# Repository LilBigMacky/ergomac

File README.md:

# ergomac
custom split ergonomic keyboard pcb

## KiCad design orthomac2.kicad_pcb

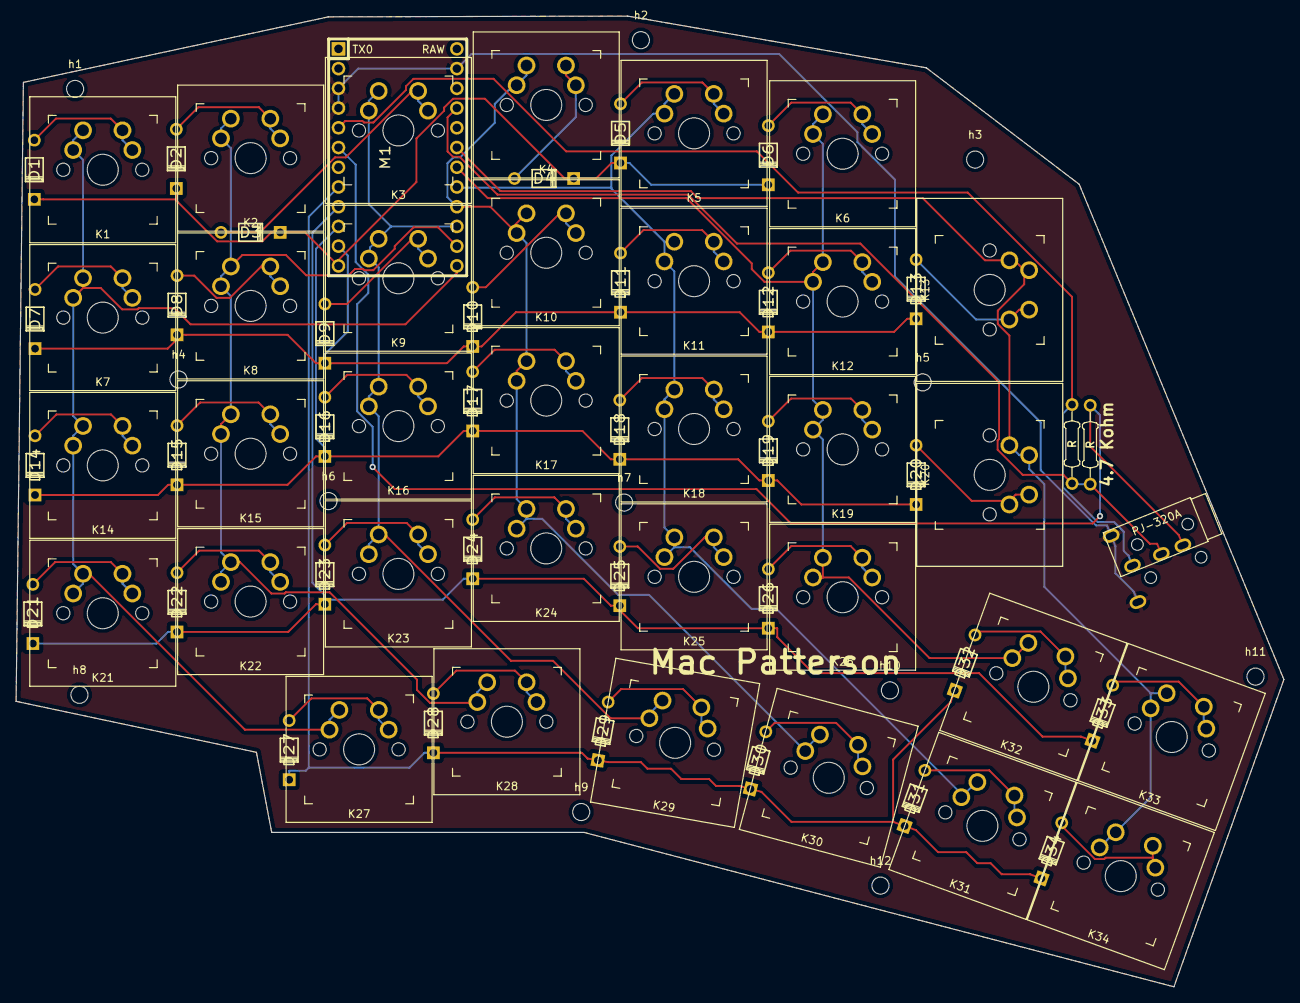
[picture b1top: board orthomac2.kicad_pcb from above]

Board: 2 copper layers, 163.2 x 125.0 mm, 84 parts (0 on the bottom side), 50 nets.

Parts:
D1, D2, D3, D4, D5, D6, D7, D8, D9, D10, D11, D12, D13, D14, D15, D16, D17, D18, D19, D20, D21, D22, D23, D24, D25, D26, D27, D28, D29, D30, D31, D32, D33, D34: D; Diode
J1: AudioJack4_Ground; TRRS-PJ-320A-dual
K1, K2, K3, K4, K5, K6, K7, K8, K9, K10, K11, K12, K14, K15, K16, K17, K18, K19, K21, K22, K23, K24, K25, K26, K27, K28, K29, K30, K31, K32, K33, K34: KEYSW; MX_reversible
K13, K20: KEYSW; MX_reversible_1.25
M1: ProMicro; ARDUINO_PRO_MICRO
R1, R2: R; Resistor
h1, h2, h3, h4, h5, h6, h7, h8, h9, h10, h11, h12: MountingHole_2.2mm_M2

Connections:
/col0: K1.1, K7.1, K14.1, K21.1, K27.1, M1.13
/col1: K2.1, K8.1, K15.1, K22.1, K28.1, M1.14
/col2: K3.1, K9.1, K16.1, K23.1, K29.1, M1.15
/col3: K4.1, K10.1, K17.1, K24.1, K30.1, M1.16
/col4: K5.1, K11.1, K18.1, K25.1, K31.1, M1.17
/col5: K6.1, K12.1, K19.1, K26.1, K32.1, M1.18
/col6: K13.1, K20.1, K33.1, K34.1, M1.19
/row0: D1.1, D2.1, D3.1, D4.1, D5.1, D6.1, M1.12
/row1: D7.1, D8.1, D9.1, D10.1, D11.1, D12.1, D13.1, M1.11
/row2: D14.1, D15.1, D16.1, D17.1, D18.1, D19.1, D20.1, M1.10
/row3: D21.1, D22.1, D23.1, D24.1, D25.1, D26.1, D33.1, M1.9
/row4: D27.1, D28.1, D29.1, D30.1, D31.1, D32.1, D34.1, M1.8
unnamed: D1.2, K1.2
unnamed: D2.2, K2.2
unnamed: D3.2, K3.2
unnamed: D4.2, K4.2
unnamed: D5.2, K5.2
unnamed: D6.2, K6.2
unnamed: D7.2, K7.2
unnamed: D8.2, K8.2
unnamed: D9.2, K9.2
unnamed: D10.2, K10.2
unnamed: D11.2, K11.2
unnamed: D12.2, K12.2
unnamed: D13.2, K13.2
unnamed: D14.2, K14.2
unnamed: D15.2, K15.2
unnamed: D16.2, K16.2
unnamed: D17.2, K17.2
unnamed: D18.2, K18.2
unnamed: D19.2, K19.2
unnamed: D20.2, K20.2
unnamed: D21.2, K21.2
unnamed: D22.2, K22.2
unnamed: D23.2, K23.2
unnamed: D24.2, K24.2
unnamed: D25.2, K25.2
unnamed: D26.2, K26.2
unnamed: D27.2, K27.2
unnamed: D28.2, K28.2
unnamed: D29.2, K29.2
unnamed: D30.2, K30.2
unnamed: D31.2, K31.2
unnamed: D32.2, K32.2
unnamed: D33.2, K33.2
unnamed: D34.2, K34.2
gnd: J1.1, M1.3, M1.4, M1.23
scl: J1.4, M1.6, R2.1
sda: J1.2, M1.5, R1.2
vcc: J1.3, M1.21, R1.1, R2.2
